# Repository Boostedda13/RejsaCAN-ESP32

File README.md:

# RejsaCAN

RejsaCAN is a 3x5 centimetre small ESP32 or ESP32-S3 based board aimed at car use that I put together for my own use in my assorted crazy car projects. The board has an onboard CAN interface and can be powered directly from the car (5-24V). It also includes the option to auto shutdown so not to drain the car battery. This is especially important if you have it plugged in to a car OBD2 connector since these always supply constant 12V power to the connector, even when the car is parked and turned off.

There is no bespoke code for the board apart from pin definitions, it's just a piece of universal hardware, but by using easy to use open source Arduino libraries it can be made to interface not only to various CAN buses, Network/Wifi and Bluetooth but to numerous sensors and other peripherals using the ESP32's built in interfaces.

You can assemble your own board if you want, you find schematics, Gerber files and bill of materials in the <a href=Schematics>schematics folder</a>. I currently have a few extra boards so if you need one or more factory assembled boards you can always contact me at magnust@gmail.com.
  
### Nice review and get started guide at cnx-software  
  
https://www.cnx-software.com/2023/05/12/rejsacan-esp32-s3-can-bus-board-arduino-car-hacking/  
  
### Navigate  
  
- <a href=./>Main page (this page)</a>  
 
- <a href=Projects%20and%20ideas>Fun projects and ideas</a>  
 
- <a href=Schematics>Schematics</a>

- <a href=Code%20Examples>Code examples</a>
 
- <a href=Tips%20to%20setup%20IDE%20and%20get%20started>Links to some different CAN libraries and tips to get started</a>  
  
-  <a href=3dprint>Examples of 3D printable housings</a>  

-  <a href=Auxiliary%20boards>Some odd auxiliary boards I made to mount an OBD2 connector, display, thermal cam...</a>  

<hr>

## Pinout  
  
See complete pinout.h https://github.com/MagnusThome/RejsaCAN-ESP32/blob/main/Schematics/

## Schematics

click to get full schematics

## The board is based around an ESP32 or ESP32-S3 chip

The ESP32-S3 is a very nice and capable chip that supports a mind boggling range of different communication standards and hardware auxiliaries making it a very versatile "hub" for shuffling data between different systems.  

- SPI bus
- I2C bus
- BLE (Bluetooth 5)
- Wifi (both as AP or client)
- Networking, everything from simple http, mqtt, ajax, ntp to running a full webserver on it with a user interface
- USB port (serial in/out and also OTG as virtual keyboard, wireless storage...)
- Analog input, PWM or analog output

## Examples

- Read CAN data and send back CAN packets to control the car (set to sport mode as default, lock doors when driving away, this is one of my current projects)
- CAN to BLE or network/Wifi bridge
- CAN interface for sniffing CAN bus with for example SavvyCAN
- Read I2C/SPI/analog sensor data and write to CAN bus for CAN bus based data loggers
- Publish live telemetric data on internet from Racechrono (I'm starting this project now)
- Drive alarm beeper or LED to show status of CAN data (like my small project Money Shift Saver and also low oil pressure warning)
- Drive high power peripherals using a driver board
- Translate CAN data between two CAN buses (like my small project Current Gear HUD here on github)

- I have already made a connector board to attach the RejsaCAN on the back of the commonly available small ILI9341 touch screen.

## Ideas for peripherals

- IR camera sensor arrays (MLX90xxx or AMG8833) to log tire, brake, drivetrain temperatures over BLE to Racechrono or CAN based loggers (like my project RejsaRubberTrac https://github.com/MagnusThome/RejsaRubberTrac)  
- Laser based TOF distance sensor to log suspension travel (I did this too with RejsaRubberTrac)  
- SPI or I2C based color displays to show CAN bus data like IC intake or oil temps or alarms  
- SPI or I2C based color displays to show live telemetric data fetched over BLE from Racechrono  
- A second CAN port  
- Driver board to drive high power items  
- Step motor drivers  
- Multiple input analog or digital boards  
   
## One of the 3D printed housings with OBD2 connector I've made

## Or just the board and screw terminals

# CAN interface

You can hook the board up straight to the car's OBD2 port or attach it directly to any CAN bus. You just need to connect the four wires. 12V power, ground, CAN high and low. There is of course a bus termination resistor on the board, it can be disabled if not needed by cutting a pcb trace and optionally mounting a pin header and jumper.

# Supply requirements (v3.5)

**Feed this board from a fused accessory circuit downstream of the vehicle's own
load-dump suppression. Do not hard-wire it upstream of a battery master / kill switch.**

That is not boilerplate, it is the condition the front end is designed to. The board is
rated **5-24 V** with a 33 V DC ceiling, which covers a 12 V system running at 14 V,
a 24 V jump start for 60 s, regulator failure at 18 V for 60 min, reverse polarity, and
ISO 7637-2 pulses 1, 2a, 3a and 3b. The clamp is a 33 V bidirectional TVS at the
connector, so a *suppressed* load dump (35 V for up to 400 ms, which is what a modern
alternator produces) is survived on voltage rating alone.

An **unsuppressed** load dump is a different event: 79-101 V for 40-400 ms, carrying
20-52 J. Opening a battery master switch with the engine running produces exactly that.
No discrete TVS of any package size absorbs it -- a 3 kW SMC part is worth about 3 J.
Surviving that case needs a series surge stopper (LTC4364 class) and roughly 150 mm2 of
board this design does not have. Since RejsaCAN is aimed at motorsport, where kill
switches are common, this restriction is the trade that was made deliberately.

24 V *systems* are out of scope. Their suppressed load dump is 58 V, which no clamp
below 58 V standoff survives, and a 60 V standoff part clamps near 97 V.

# Functionality

The idea was to make an as small as possible CAN + ESP32 board with as many cool and useful "good to have" functions as possible included. You know as well as I do that when tinkering around you suddenly get a new idea and need x or y :-D 

## Auto shutdown

When the engine is running and charging the car battery the incoming voltage used to power the board is a little bit higher than when the engine is stopped. This can be used to automate board shutdown so not to drain the car battery. As default the on board DC-DC power circuit will shutdown the whole board when the power voltage is below the "engine is running" threshold and boot up the board when it is above. But you can run the board in a number of other ways too, for example using ESP32 sleep mode, waking it and putting it to sleep depending on CAN traffic, voltage level from the car, delays and so on.

- An output (FORCE_ON GPIO17) can be pulled high to keep the board running even if the car voltage drops below the threshold (instead of disabling the auto shutdown fully on the pcb by shorting the "ALWAYS ON" bridge). The ESP32 can keep this pin high even during sleep.

- A digital input (SENSE_V_DIG GPIO08) monitors if the car voltage is above or below the "engine running" threshold. This can both be used to trigger waking the board from sleep or just as a simple check if the engine is charging the car battery or not.  

- The voltage from the car can be monitored using analog input (SENSE_V_ANA GPIO9) to check not only charging level but also battery discharge level when parked, health of charging, health of battery, detect large loads being switched on or off in the car and so on.

- The CAN data input (CAN_RX GPIO13) can also be used to trigger waking up the board from sleep as soon as CAN traffic is detected.

Either one can just let the board turn on and off with the auto shutdown hardware circuitry straight out of the box or you can run it in combination with software. For example, when the car voltage rises and the board boots you can pull FORCE_ON high to make sure the board keeps running even if there is a drop of voltage, for example due to red light start/stop functionality in the car or modern cars turning down battery charging even when driving. Then you just monitor either the threshold with SENSE_V_DIG or set your own thresholds using SENSE_V_ANA and then add your own timer delays or whatever. And of course, you can use CAN to check if the car is stopped in a multitude of ways, rpm, speed, gear...

### Fine tuning on/off voltage thresholds  

If your car has a more modern battery type than the old acid/led type or if it does the battery charging slightly different you might want to adjust the on/off voltage thresholds. If you keep R5 as 33k and adjust R4 you can get these switch-on and -off voltages:

| **R4** | **Turn on at** | **Turn off at** |
|-------:|---------------:|----------------:|
| 91k    | 13,7V           | 13,0V            |
| 90k    | 13,6V           | 12,9V            |
| 89k    | 13,5V           | 12,8V            |
| 88k    | 13,4V           | 12,7V            |
| 87k    | 14,3V           | 12,6V            |
| 86k    | 13,2V           | 12,5V            |
| 85k    | 13,1V           | 12,4V            |

### 24V vehicles

For 24V vehicles you can change the on/off voltage threshold by soldering on a resistor at the empty "ADJUST" position. I don't know what voltages one can expect in these vehicles while charging and not charging the battery so I have no idea what an appropriate resistor value should be there. 

## "Good to haves"

### Three on board LEDs  

- Green power LED that shows if the board is turned on or not. If using the auto shutdown the green LED (and the board) will be turned on and off depending on if the car voltage is over or under the auto start/shutdown threshold.

- Blue LED to use for anything you fancy (BLUE_LED GPIO10) (this one is red on some boards due to the blue led being out of stock lately)
- Yellow LED to use for anything (YELLOW_LED GPIO11)

### Extra UART RX/TX

The ESP32-S3 has a built in USB port for uploading firmware, OTG support(!) and general communication. But on the board's rear there are breakout pads for a second UART (TXD0 and RXD0) so you can use this as a serial port and the board's USB port for other tasks like JTAG or OTG, acting as a peripheral keyboard, mouse, wireless storage and so on.

### 3V3 HIGH DRIVER

The GPIO pins on the ESP32-S3 can, in addition to general digital circuitry, also drive 10-20mA loads like LEDs and other smaller loads. But on the RejsaCAN board there is an added more powerful driver circuit that can drive slightly larger loads of a few hundred mA at 3,3V. This can be used for different things like powering external sensors or a small display that you want to be able to shutdown fully to minimize power consumption while in sleep mode for example. This 3V3_SWITCHED output is controlled by HI_DRIVER (GPIO21). The ESP32-S3 can keep this on or off when in sleep mode.

There is also a 3,3V power output pad in the row of connection pads on the board that is turned on whenever the board is running. Keep in mind that this is _not_ a 3V3 input to drive the board, it is only an output to drive external I2C, SPI and other sensors.

### SD card reader

The ESP32-S3 has an SD micro card reader on the rear of the pcb. It is connected to SPI and select SD_CARD (GPIO45)

### Other general IO pins
  
All the GPIOs found on the row of connector pads are general purpose. They can be PWM, analog, digital in/out whatever, special protocols driving or reading most things you can think of. But for ease of use for me with occasional lousy memory I have marked some default uses:  
  
I2C SDA  (GPIO1)  (A0)  
I2C SCL  (GPIO2)  (A1)  
GND  
3V3  
  
SPI MISO / MTDI  (GPIO41)  
SPI CLK  / MTCK  (GPIO39)  
SPI MOSI / MTDO  (GPIO40)  
  
General  (GPIO12)  
General  (GPIO48)  
General  (GPIO47)  
High driver switched output max 500mA  (GPIO21)  

On the rear side of the pcb you can get to a few extra pins but it's not possible to solder pin headers here due to the esp-module being on the other side of the board where these pads are.  
  
General  (GPIO6)  (A5)  
General  (GPIO7)  (A6)  
General  (GPIO15)  
General  (GPIO16)  
MTMS  (GPIO42)  
PROG  (GPIO0)  
JTAG_ENABLE  (GPIO3)  
TXD0   
RXD0  

### CAN bus

As mentioned earlier the CAN_RX (GPIO13) can wake the ESP32-S3 from sleep whenever any traffic is seen on the CAN bus.

To minimize power draw when not using the CAN bus, for example not listening to the bus to detect traffic to wake the ESP32 from sleep mode, the CAN transceiver can be put in standby mode by pulling CAN_RS (GPIO38) high. The ESP32-S3 can keep this pin high even when in sleep mode reducing the complete boards power draw to an absolute minimum.

The rise time of the CAN transceiver chip can be changed pulling CAN_RS (GPIO38) low. Default is keeping the pin unmodified in high impedance state for an optimal not-to-fast rise time setting. See specs for the transceiver chip SN65HVD230DR.

### JTAG

You can either run JTAG over the USB port or optionally keep the USB port free by connecting your JTAG hardware to MTDI, MTDO, MTCK and MTMS on the board. Note that MTMS is only available on the board's rear. The other are available in the row of connecting pads. Incidentally the MTDI, MTDO and MTCK are the same as the SPI default pins.

To enable JTAG mode you need to pull the JTAG_ENABLE pad, found on the rear of the board, high or low at boot.

### Board version

On v3.x boards you can programmatically check what version of the board your code is running on and adjust accordingly for the small changes that have been made on the boards. Set GPIO4 and GPIO5 to input pullup and check if the inputs are high or low.

- v3.1 = GPIO4 low and GPIO5 high  
- v3.2 = GPIO4 high and GPIO5 low  

### Changes

#### from v3.1 to v3.2

- Added RS control of the CAN chip to set both standby mode and faster rise times
- Added better over voltage protection on power from the car
- Upgraded over voltage protection on USB power
- Enabling ALWAYS_ON is now done by shorting two clearly marked pads on the rear of the board
- An added empty spot for resistor R19 ADJUST which can be added to lower the start/stop voltage threshold for the board
- For panic situations when you need more pins ;-) the GPIO6, GPIO7, GPIO15 and GPIO16 are available as unmarked pads but only on the rear of the board
  
#### From v2.3 to v.2.4
  
- Upgraded over voltage protection on USB power  

#### From v2.4 to v.2.5 and 3.2 to 3.3
  
- DC-DC converter supports 24V input. The auto switch on/off threshold can be changed by changing two resistor values.  

## Power consumption  
 
At 14V the complete board draws *on average* roughly:  
- Bluetooth turned on but no connections = 16mA (+ 4mA for power LED)
- Wifi turned on as AP with local web server but no connections = 46mA (+ 4mA for power LED)
- No wifi or Bluetooth = 14mA (+ 4mA for power LED)
- Sleep = 3mA (+ 4mA for power LED). Note that the CAN transceiver is fully active and the DC-DC buck converter probably has some idle draw also.
- Sleep and CAN transceiver put in standby = hmmm, must test this, a fraction of a mA is my guess.
   
## Housing

Check out 3D printable housings in the <a href=3dprint>the 3D-print directory</a>. So far I've made one housing where you connect using a cable and another one with an integrated OBD2 connector to plug directly into the car.

## Connecting the board

When not using the housing with an integrated OBD2 connector or the screw terminals as seen in the picture above I've used a widely available OBD2 splitter cable (flat cable) that has one male and two female connectors. I hook up the male connector to the car, cut off one female connector and wire the remaining pig tail cable into the RejsaCAN board and one female connector is then free for other equipment to hook up to the car.

Picture showing what wires to use but please measure your cable and don't trust all these splitter cables to be 100% identical. (the second female splitter connector is not visible in pic)

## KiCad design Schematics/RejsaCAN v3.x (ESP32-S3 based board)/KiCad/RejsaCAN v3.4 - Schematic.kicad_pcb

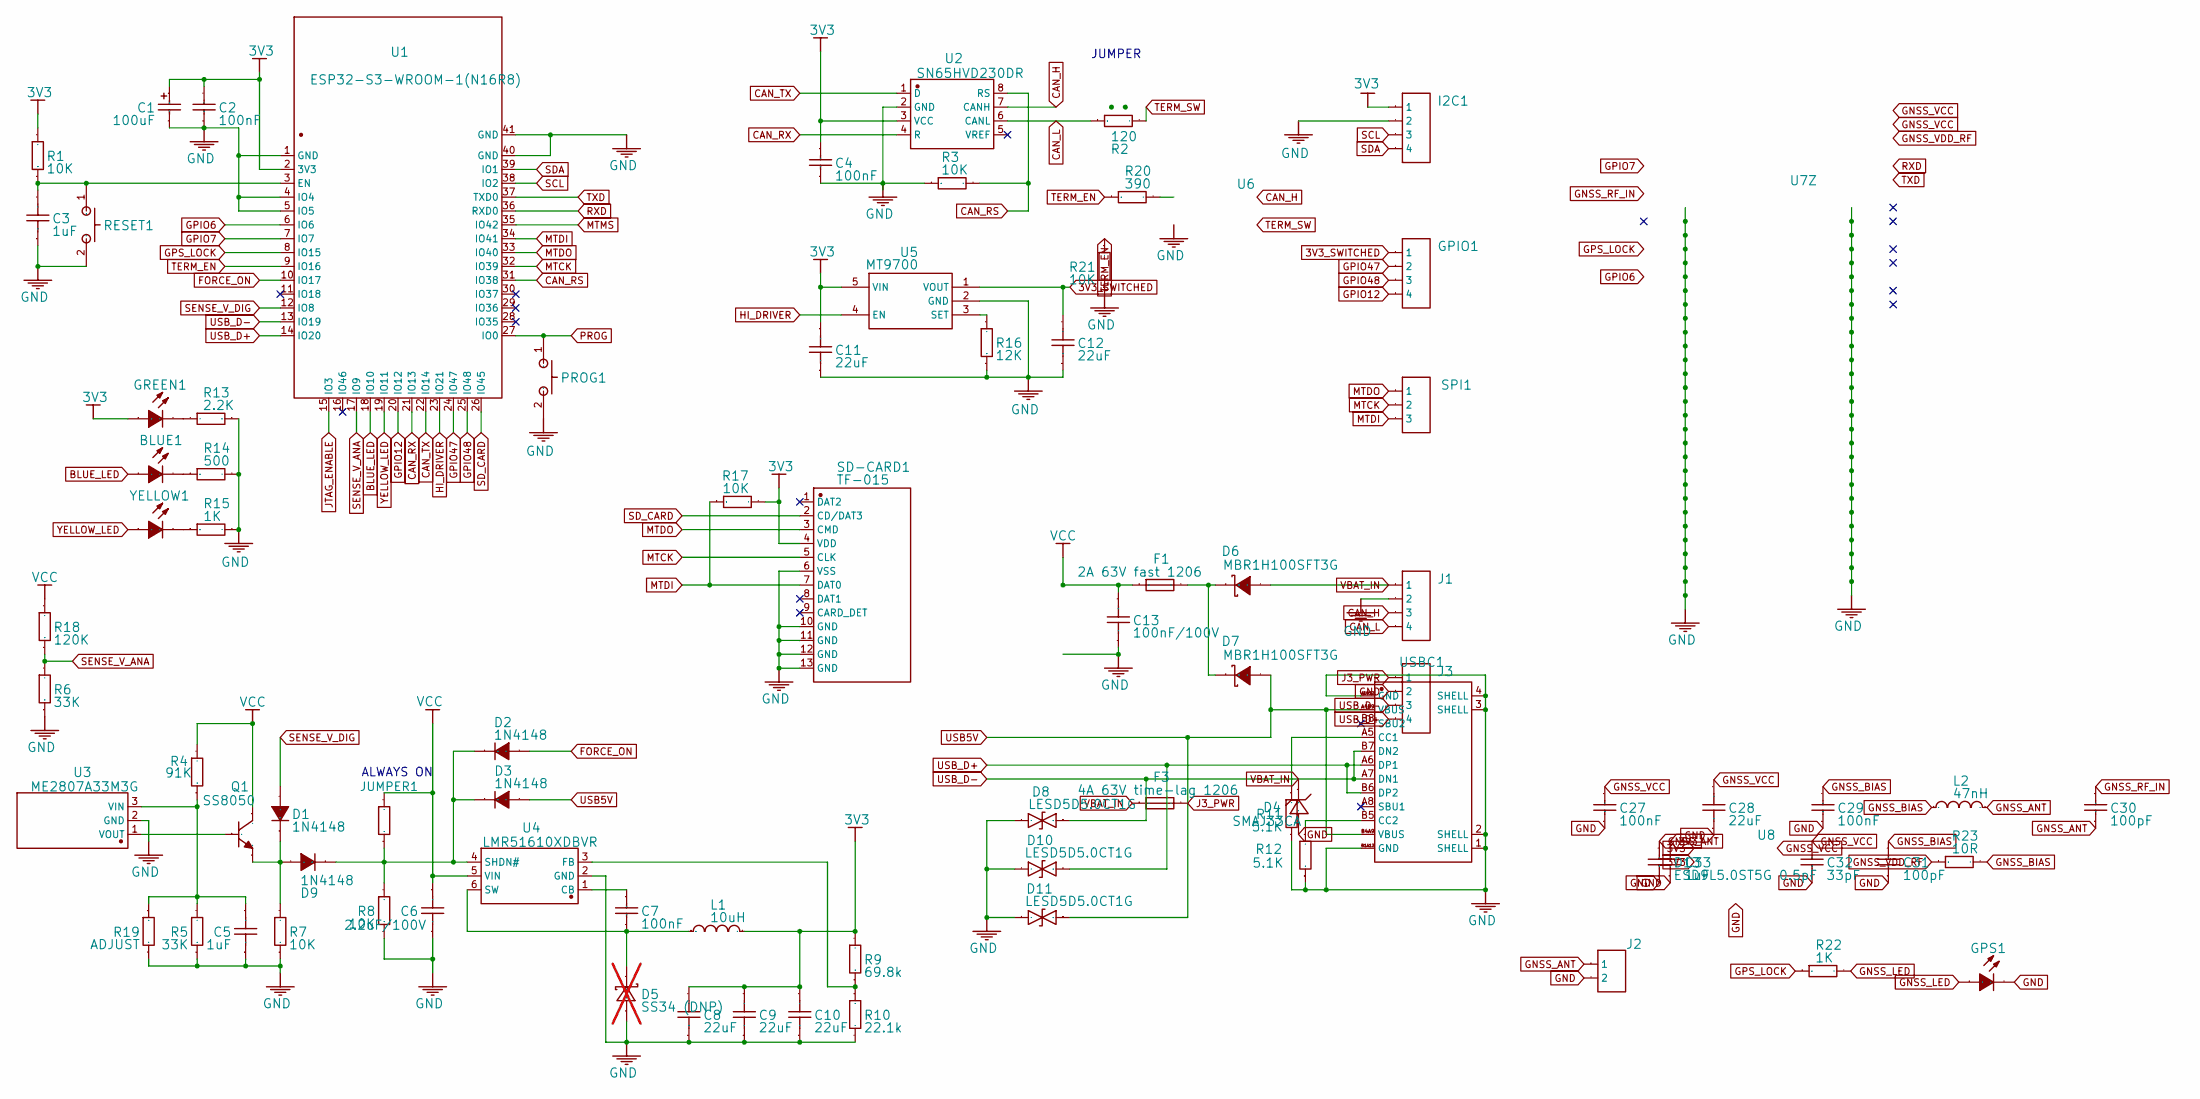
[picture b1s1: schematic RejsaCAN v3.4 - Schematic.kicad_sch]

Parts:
BLUE1: 19-217/BHC-ZL1M2RY/3T; LED_0603_1608Metric; Manufacturer Part 19-217/BHC-ZL1M2RY/3T
C1: 100uF; CP_EIA-3528-21_Kemet-B; Manufacturer Part TAJB107K006RNJ
C2, C4, C7, C27, C29: 100nF; C_0402_1005Metric; Manufacturer Part CL05B104KO5NNNC
C3, C5, C33: 1uF; C_0402_1005Metric; Manufacturer Part CL05A105KA5NQNC
C6: 2.2uF/100V; C_1210_3225Metric; Manufacturer Part CL32B225KCJSNNE
C8, C9, C10, C11, C12, C28: 22uF; C_0603_1608Metric; Manufacturer Part CL10A226MQ8NRNC
C13: 100nF/100V; C_0603_1608Metric; Manufacturer Part CL10B104KC8NNNC
C30, C31: 100pF; C_0402_1005Metric; Manufacturer Part 0402CG101J500NT
C32: 33pF; C_0402_1005Metric; Manufacturer Part 0402CG330J500NT
D1, D2, D3, D9: 1N4148; D_SOD-323; Manufacturer Part 1N4148WS
D4: SMAJ33CA; D_SMA; Manufacturer Part SMAJ33CA
D5: SS34 (DNP); D_SMA; Manufacturer Part SS34; not fitted
D6, D7: MBR1H100SFT3G; D_SOD-123F; Manufacturer Part MBR1H100SFT3G
D8, D10, D11: LESD5D5.0CT1G; D_SOD-523; Manufacturer Part LESD5D5.0CT1G
D13: ESD9L5.0ST5G 0.5pF; D_0402_1005Metric; Manufacturer Part ESD9L5.0ST5G
F1: 2A 63V fast 1206; Fuse_1206_3216Metric; Manufacturer Part 0466002.NRHF
F3: 4A 63V time-lag 1206; Fuse_1206_3216Metric; Manufacturer Part 1206T4A63V
GPIO1: HDR-M-2.54_1x4; PinHeader_1x04_P2.54mm_Vertical; Manufacturer Part B-2100S04P-A110
GPS1: Blue LED; LED_0603_1608Metric; Manufacturer Part 19-217/BHC-ZL1M2RY/3T
GREEN1: 19-217/GHC-YR1S2/3T; LED_0603_1608Metric; Manufacturer Part 19-217/GHC-YR1S2/3T
I2C1: HDR-M-2.54_1x4; PinHeader_1x04_P2.54mm_Vertical; Manufacturer Part B-2100S04P-A110
J1: Micro-Fit 3.0 4P R/A; Molex_Micro-Fit_3.0_43045-0400_2x02_P3.00mm_Horizontal; Manufacturer Part 43045-0400
J2: U.FL; U.FL_Hirose_U.FL-R-SMT-1_Vertical; Manufacturer Part U.FL-R-SMT-1(10)
J3: JST-XH 4P LTE; JST_XH_B4B-XH-A_1x04_P2.50mm_Vertical; Manufacturer Part B4B-XH-A(LF)(SN)
JUMPER1: -; R_0402_1005Metric; Manufacturer Part DNP
L1: 10uH; L_Sunltec_SLP6028S_6.0x6.0mm; Manufacturer Part SLP6028S100MTT
L2: 47nH; L_0402_1005Metric; Manufacturer Part LQW15AN47NJ00D
PROG1: GT-TC029B-H025-L1N; SW_Push_GSwitch_GT-TC029B; Manufacturer Part GT-TC029B-H025-L1N
Q1: SS8050; SOT-23; Manufacturer Part SS8050
R1, R3, R7, R8, R17, R21: 10K; R_0402_1005Metric; Manufacturer Part 0402WGF1002TCE
R2: 120; R_1206_3216Metric; Manufacturer Part RTT061200FTP
R4: 91K; R_0402_1005Metric; Manufacturer Part 0402WGF9102TCE
R5, R6: 33K; R_0402_1005Metric; Manufacturer Part 0402WGF3302TCE
R9: 69.8k; R_0402_1005Metric; Manufacturer Part 0402WGF6982TCE
R10: 22.1k; R_0402_1005Metric; Manufacturer Part 0402WGF2212TCE
R11, R12: 5.1K; R_0402_1005Metric; Manufacturer Part 0402WGF5101TCE
R13: 2.2K; R_0402_1005Metric; Manufacturer Part 0402WGF2201TCE
R14: 500; R_0402_1005Metric; Manufacturer Part 0402WGF4700TCE
R15, R22: 1K; R_0402_1005Metric; Manufacturer Part 0402WGF1001TCE
R16: 12K; R_0402_1005Metric; Manufacturer Part 0402WGF1202TCE
R18: 120K; R_0402_1005Metric; Manufacturer Part 0402WGF1203TCE
R19: ADJUST; R_0402_1005Metric; Manufacturer Part 0402WGF9102TCE
R20: 390; R_0402_1005Metric; Manufacturer Part 0402WGF3900TCE
R23: 10R; R_0402_1005Metric; Manufacturer Part 0402WGF100JTCE
RESET1: GT-TC029B-H025-L1N; SW_Push_GSwitch_GT-TC029B; Manufacturer Part GT-TC029B-H025-L1N
SD-CARD1: TF-015; microSD_ATOM_MR01A-01211; Manufacturer Part TF-015
SPI1: HDR-M-2.54_1x3; PinHeader_1x03_P2.54mm_Vertical; Manufacturer Part 2.54mm 1x3 header
U1: ESP32-S3-WROOM-1(N16R8); ESP32-S3-WROOM-1_RejsaCAN; Manufacturer Part ESP32-S3-WROOM-1-N16R8
U2: SN65HVD230DR; SOIC-8_RejsaCAN_5.544mm; Manufacturer Part SN65HVD230DR
U3: ME2807A33M3G; SOT-23; Manufacturer Part ME2807A33M3G
U4: LMR51610XDBVR; TSOT-23-6; Manufacturer Part LMR51610XDBVR
U5: MT9700; SOT-23-5; Manufacturer Part MT9700
U6: AQY212GS; SOP-4_3.8x4.1mm_P2.54mm; Manufacturer Part AQY212GS
U7: LG290P03AAMD; Manufacturer Part LG290P03AAMD
U8: RT9013-33GB; SOT-23-5; Manufacturer Part RT9013-33GB
USBC1: GT-USB-7010ASV; USB_C_Receptacle_GT-USB-7010ASV_MergedPins; Manufacturer Part GT-USB-7010ASV
YELLOW1: 19-213/Y2C-CQ2R2L/3T(CY); LED_0603_1608Metric; Manufacturer Part 19-213/Y2C-CQ2R2L/3T(CY)

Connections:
3V3: C1.1, C2.2, C4.2, C8.2, C9.2, C10.2, C11.2, C33.2, GREEN1.1 (A), I2C1.1, L1.2, R1.2, R9.2, R17.2, SD-CARD1.4 (VDD), U1.2 (3V3), U2.3 (VCC), U5.5 (VIN), U8.1 (VIN), U8.3 (EN)
3V3_SWITCHED: C12.2, GPIO1.1, U5.1 (VOUT)
BLUE_LED: BLUE1.1 (A), U1.18 (IO10)
CAN_H: J1.3, U2.7 (CANH), U6.4
CAN_L: J1.4, R2.1, U2.6 (CANL)
CAN_RS: R3.2, U1.31 (IO38), U2.8 (RS)
CAN_RX: U1.21 (IO13), U2.4 (R)
CAN_TX: U1.22 (IO14), U2.1 (D)
FORCE_ON: D2.2 (A), U1.10 (IO17)
GND: C1.2, C2.1, C3.1, C4.1, C5.1, C6.1, C8.1, C9.1, C10.1, C11.1, C12.1, C13.1, C27.1, C28.1, C29.1, C31.1, C32.1, C33.1, D4.2, D5.2 (A), D8.2, D10.2, D11.2, D13.1, GPS1.2 (C), I2C1.2, J1.2, J2.2, J3.2, PROG1.2, R3.1, R5.1, R6.1, R7.1, R8.1, R10.2, R11.1, R12.1, R13.1, R14.2, R15.2, R16.1, R19.2, R21.1, RESET1.2, SD-CARD1.6 (VSS), SD-CARD1.10 (GND), SD-CARD1.11 (GND), SD-CARD1.12 (GND), SD-CARD1.13 (GND), U1.1 (GND), U1.4 (IO4), U1.5 (IO5), U1.40 (GND), U1.41 (GND), U2.2 (GND), U3.2 (GND), U4.2 (GND), U5.2 (GND), U6.2, U7.10 (GND_1), U7.12 (GND_1__1), U7.13 (GND_1__2), U7.24 (GND_1__3), U7.25 (GND_1__4), U7.26 (GND_1__5), U7.27 (GND_1__6), U7.28 (GND_1__7), U7.29 (GND_1__8), U7.30 (GND_1__9), U7.31 (GND_1__10), U7.32 (GND_1__11), U7.33 (GND_1__12), U7.34 (GND_1__13), U7.35 (GND_1__14), U7.36 (GND_1__15), U7.37 (GND_1__16), U7.38 (GND_1__17), U7.39 (GND_1__18), U7.40 (GND_1__19), U7.41 (GND_1__20), U7.42 (GND_1__21), U7.43 (GND_1__22), U7.44 (GND_1__23), U7.45 (GND_1__24), U7.46 (GND_1__25), U7.47 (GND_1__26), U7.48 (GND_1__27), U7.49 (GND_1__28), U7.50 (GND_1__29), U7.51 (GND_2), U7.52 (GND_2__1), U7.53 (GND_2__2), U7.54 (GND_2__3), U7.55 (GND_2__4), U7.56 (GND_2__5), U7.57 (GND_2__6), U7.58 (GND_2__7), U7.59 (GND_2__8), U7.60 (GND_2__9), U7.61 (GND_2__10), U7.62 (GND_2__11), U7.63 (GND_2__12), U7.64 (GND_2__13), U7.65 (GND_2__14), U7.66 (GND_2__15), U7.67 (GND_2__16), U7.68 (GND_2__17), U7.69 (GND_2__18), U7.70 (GND_2__19), U7.71 (GND_2__20), U7.72 (GND_2__21), U7.73 (GND_2__22), U7.74 (GND_2__23), U7.75 (GND_2__24), U7.76 (GND_2__25), U7.77 (GND_2__26), U7.78 (GND_2__27), U7.79 (GND_2__28), U8.2 (GND), USBC1.1 (SHELL), USBC1.2 (SHELL), USBC1.3 (SHELL), USBC1.4 (SHELL), USBC1.A1B12 (GND), USBC1.B1A12 (GND)
GNSS_ANT: C30.1, D13.2, J2.1, L2.2
GNSS_BIAS: C29.2, C31.2, L2.1, R23.2
GNSS_LED: GPS1.1 (A), R22.2
GNSS_RF_IN: C30.2, U7.11 (RF_IN)
GNSS_VCC: C27.2, C28.2, C32.2, U7.22 (V_BCKP), U7.23 (VCC), U8.5 (VOUT)
GNSS_VDD_RF: R23.1, U7.9 (VDD_RF)
GPIO6: U1.6 (IO6), U7.3 (1PPS)
GPIO7: U1.7 (IO7), U7.8 (~RESET)
GPIO12: GPIO1.4, U1.20 (IO12)
GPIO47: GPIO1.2, U1.24 (IO47)
GPIO48: GPIO1.3, U1.25 (IO48)
GPS_LOCK: R22.1, U1.8 (IO15), U7.14 (RTK_STAT/ANT_ON)
HI_DRIVER: U1.23 (IO21), U5.4 (EN)
JTAG_ENABLE: U1.15 (IO3)
MTCK: SD-CARD1.5 (CLK), SPI1.2, U1.32 (IO39)
MTDI: R17.1, SD-CARD1.7 (DAT0), SPI1.3, U1.34 (IO41)
MTDO: SD-CARD1.3 (CMD), SPI1.1, U1.33 (IO40)
MTMS: U1.35 (IO42)
unnamed: BLUE1.2 (C), R14.1
unnamed: D1.1 (K), D9.2 (A), Q1.2 (E), R7.2
unnamed: D2.1 (K), D3.1 (K), D9.1 (K), JUMPER1.1, R8.2, U4.4 (SHDN#)
unnamed: C7.1, D5.1 (K), L1.1, U4.6 (SW)
unnamed: D6.1 (K), D7.1 (K), F1.2
unnamed: GREEN1.2 (C), R13.2
unnamed: Q1.1 (B), U3.1 (VOUT)
unnamed: R20.2, U6.1
unnamed: C3.2, R1.1, RESET1.1, U1.3 (EN)
unnamed: C5.2, R4.1, R5.2, R19.1, U3.3 (VIN)
unnamed: C7.2, U4.1 (CB)
unnamed: R9.1, R10.1, U4.3 (FB)
unnamed: R16.2, U5.3 (SET)
unnamed: R11.2, USBC1.A5 (CC1)
unnamed: R12.2, USBC1.B5 (CC2)
unnamed: R15.1, YELLOW1.2 (C)
PROG: PROG1.1, U1.27 (IO0)
RXD: U1.36 (RXD0), U7.20 (TXD1)
SCL: I2C1.3, U1.38 (IO2)
SDA: I2C1.4, U1.39 (IO1)
SD_CARD: SD-CARD1.2 (CD/DAT3), U1.26 (IO45)
SENSE_V_ANA: R6.2, R18.1, U1.17 (IO9)
SENSE_V_DIG: D1.2 (A), U1.12 (IO8)
TERM_EN: R20.1, R21.2, U1.9 (IO16)
TERM_SW: R2.2, U6.3
TXD: U1.37 (TXD0), U7.21 (RXD1)
USB_D+: D10.1, J3.4, U1.14 (IO20), USBC1.A6 (DP1), USBC1.B6 (DP2)
VCC: C6.2, C13.2, F1.1, JUMPER1.2, Q1.3 (C), R4.2, R18.2, U4.5 (VIN)
YELLOW_LED: U1.19 (IO11), YELLOW1.1 (A)

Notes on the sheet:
ALWAYS ON
JUMPER

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
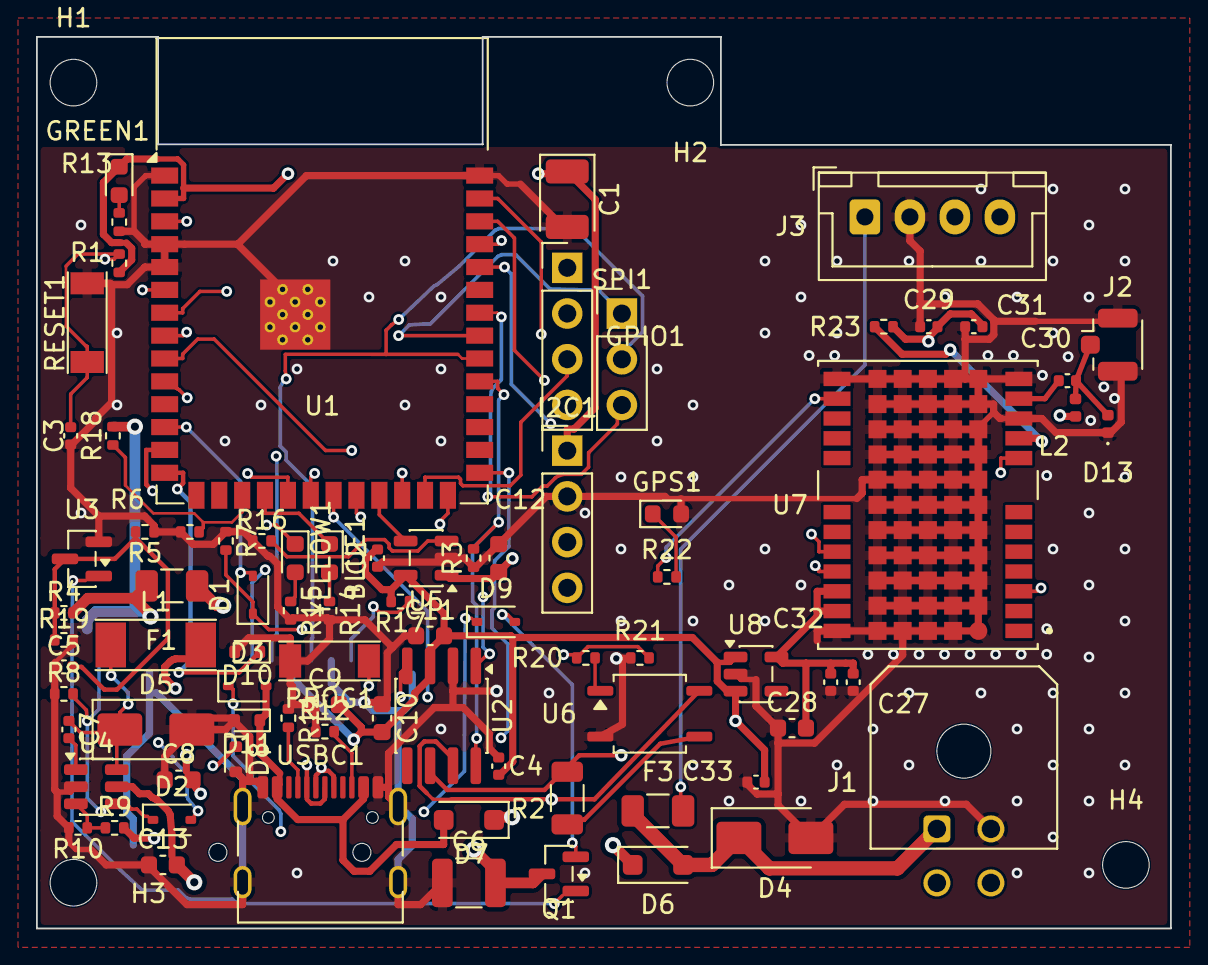
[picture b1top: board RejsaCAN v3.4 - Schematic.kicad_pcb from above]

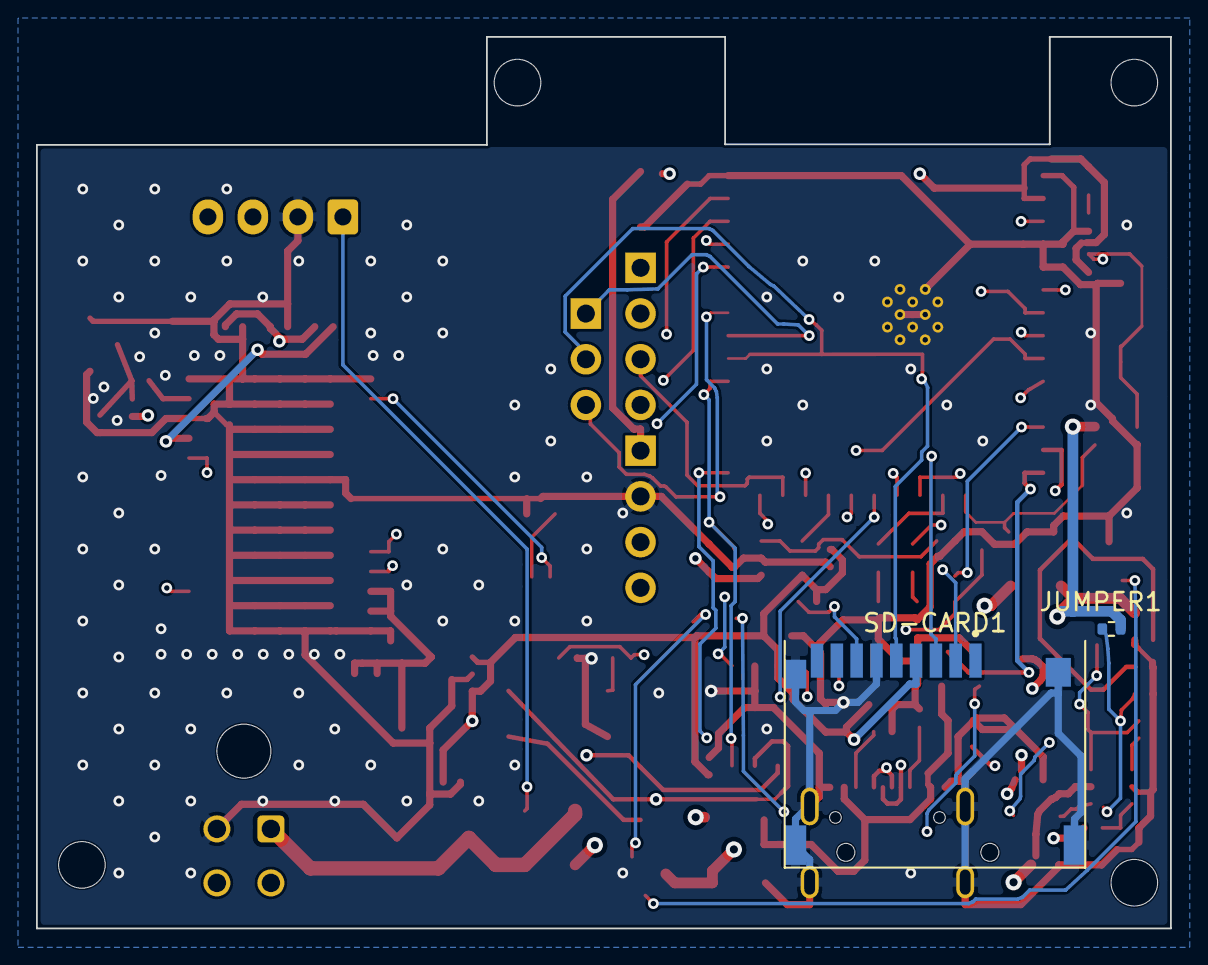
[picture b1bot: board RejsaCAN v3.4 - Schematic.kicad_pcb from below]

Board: 4 copper layers, 63.0 x 49.5 mm, 87 parts (2 on the bottom side), 59 nets.

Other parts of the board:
H1, H2, H3, H4: MountingHole_2.59mm_NPTH

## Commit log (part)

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2026-05-16 Add RejsaCAN v3.4 schematic and converter
    Add Eagle schematic for RejsaCAN v3.4 (ESP32-S3 based board) and a converter toolchain. Includes the .sch file and a converter directory with convert.py, easyeda_parser.py, eagle_emitter.py and a REA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
